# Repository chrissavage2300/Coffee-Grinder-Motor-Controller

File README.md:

# Coffee-Grinder-Motor-Controller

This is just a simple project where I retrofitted a hand crank grinder with a powerful gear motor.

Motor Used: https://www.servocity.com/118-rpm-hd-premium-planetary-gear-motor

Angle Bracket: https://www.servocity.com/90-single-angle-short-channel-bracket

Mount: https://www.servocity.com/hd-premium-planetary-gear-motor-mount-face-thru-hole

The software works as follows: Ramps up within a second or two from 25% to 100% full speed and then counts when the current goes below a minimum value. Once the current goes below that value, it shuts the motor off and waits for the user to press a button again. I had to measure the current using debugging and then average it out in excel to find a minimum value for when the coffee is ground.  During grinding the current is mostly higher than this min, so it wont trigger, but when the grinder is idling, it will hit that minumum more often.

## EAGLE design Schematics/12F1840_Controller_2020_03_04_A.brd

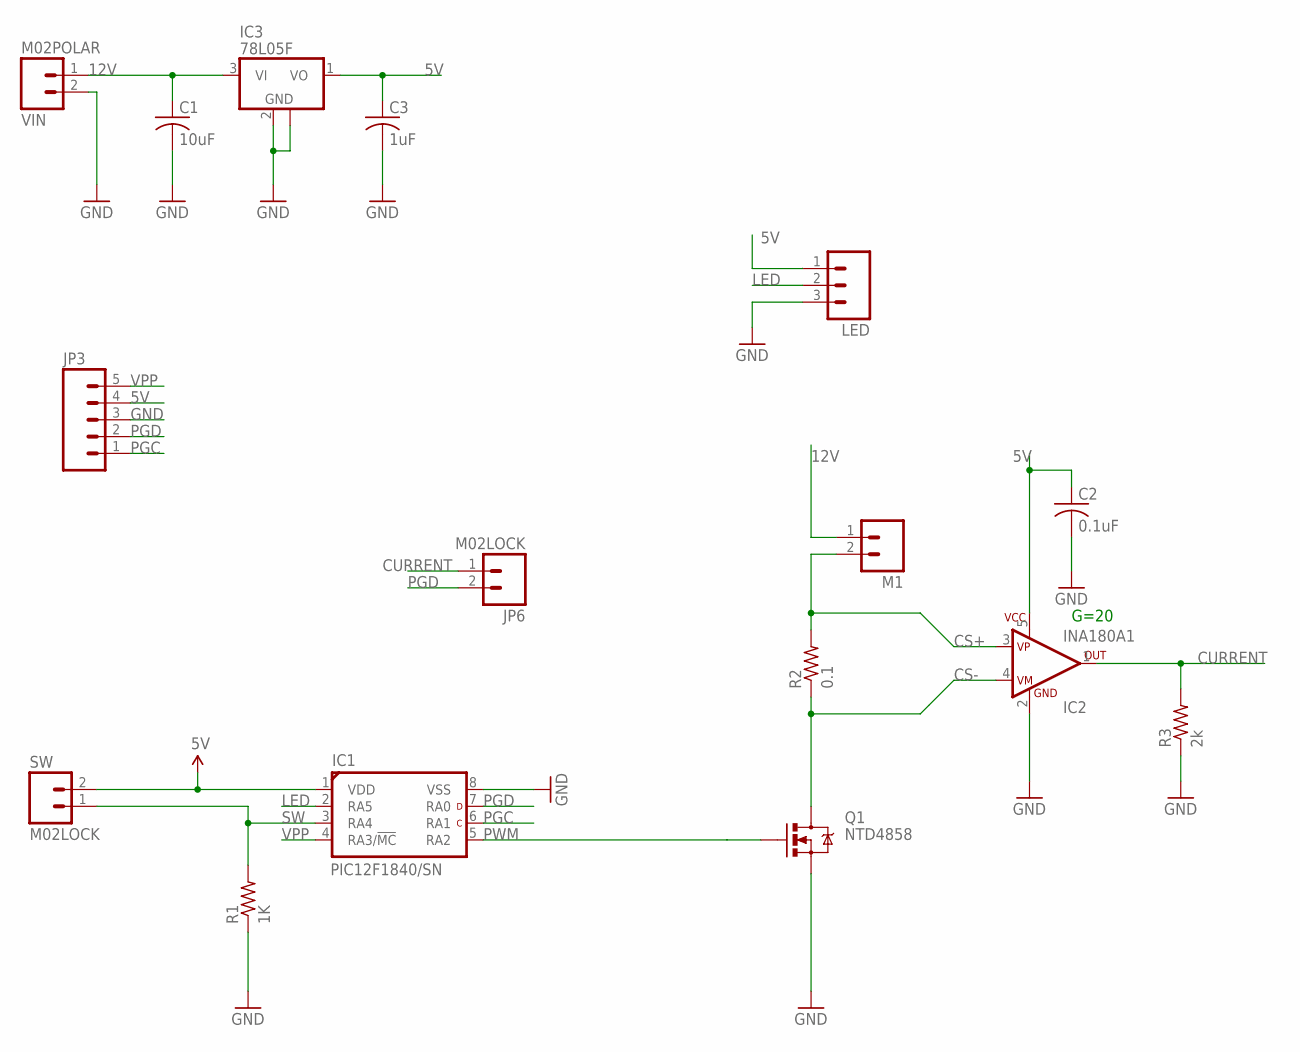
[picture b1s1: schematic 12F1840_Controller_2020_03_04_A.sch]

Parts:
C1: 10uF; C1206
C2: 0.1uF; C1206
C3: 1uF; C1206
IC1: PIC12F1840/SN; SOIC8-SN
IC2: INA180A1; SOT23-5
IC3: 78L05F; SOT89
JP3: M05LOCK; 1X05_LOCK
JP6: M02LOCK; 1X02_LOCK
LED: M03PTH; 1X03
M1: M02POLAR; MOLEX-1X2
Q1: NTD4858; DPAK
R1: 1K; R1206
R2: 0.1; R2512
R3: 2k; R1206
SW: M02LOCK; 1X02_LOCK
VIN: M02POLAR; MOLEX-1X2

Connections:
5V: C2.1, C3.1, IC1.1 (VDD), IC2.5 (V+), IC3.1 (VO), JP3.4, LED.1, SW.2
12V: C1.1, IC3.3 (VI), M1.1, VIN.1
CS+: IC2.3 (VP), M1.2, R2.2
CS-: IC2.4 (VM), Q1.4 (D), R2.1
CURRENT: IC2.1 (OUT), JP6.1, R3.2
GND: C1.2, C2.2, C3.2, IC1.8 (VSS), IC2.2 (V-), IC3.2 (GND), IC3.2@1 (GND), JP3.3, LED.3, Q1.3 (S), R1.1, R3.1, VIN.2
LED: IC1.2 (RA5), LED.2
PGC: IC1.6 (RA1), JP3.1
PGD: IC1.7 (RA0), JP3.2, JP6.2
PWM: IC1.5 (RA2), Q1.1 (G)
SW: IC1.3 (RA4), R1.2, SW.1
VPP: IC1.4 (RA3/!MC!), JP3.5

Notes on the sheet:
G=20

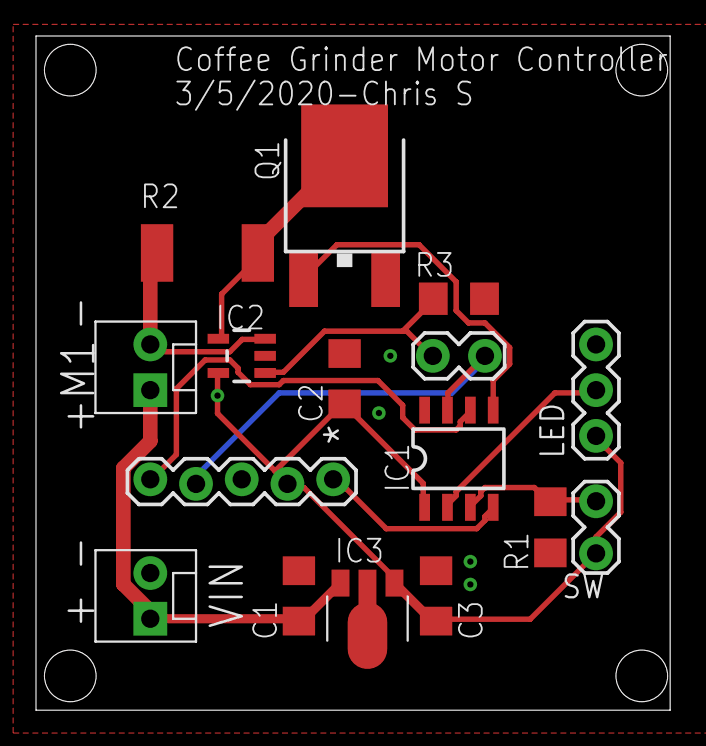
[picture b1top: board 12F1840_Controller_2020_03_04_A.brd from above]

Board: 2 copper layers, 35.2 x 37.5 mm, 16 parts (0 on the bottom side), 12 nets.

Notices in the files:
parts and their libraries:
SparkFun-Connectors: Licensing: Creative Commons ShareAlike 4.0 International - https://creativecommons.org/licenses/by-sa/4.0
